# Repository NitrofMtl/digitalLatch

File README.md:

# digitalLatch

use digital latch 74ls259 to control 16 relay

With 2 74ls259 digital latch, and some logic gate, 7 GPIO pins, control 16 relay ou other type of digital outputs.
Add one more pin and 2 others 74ls259 and double to 32 outpus. Shematic included.

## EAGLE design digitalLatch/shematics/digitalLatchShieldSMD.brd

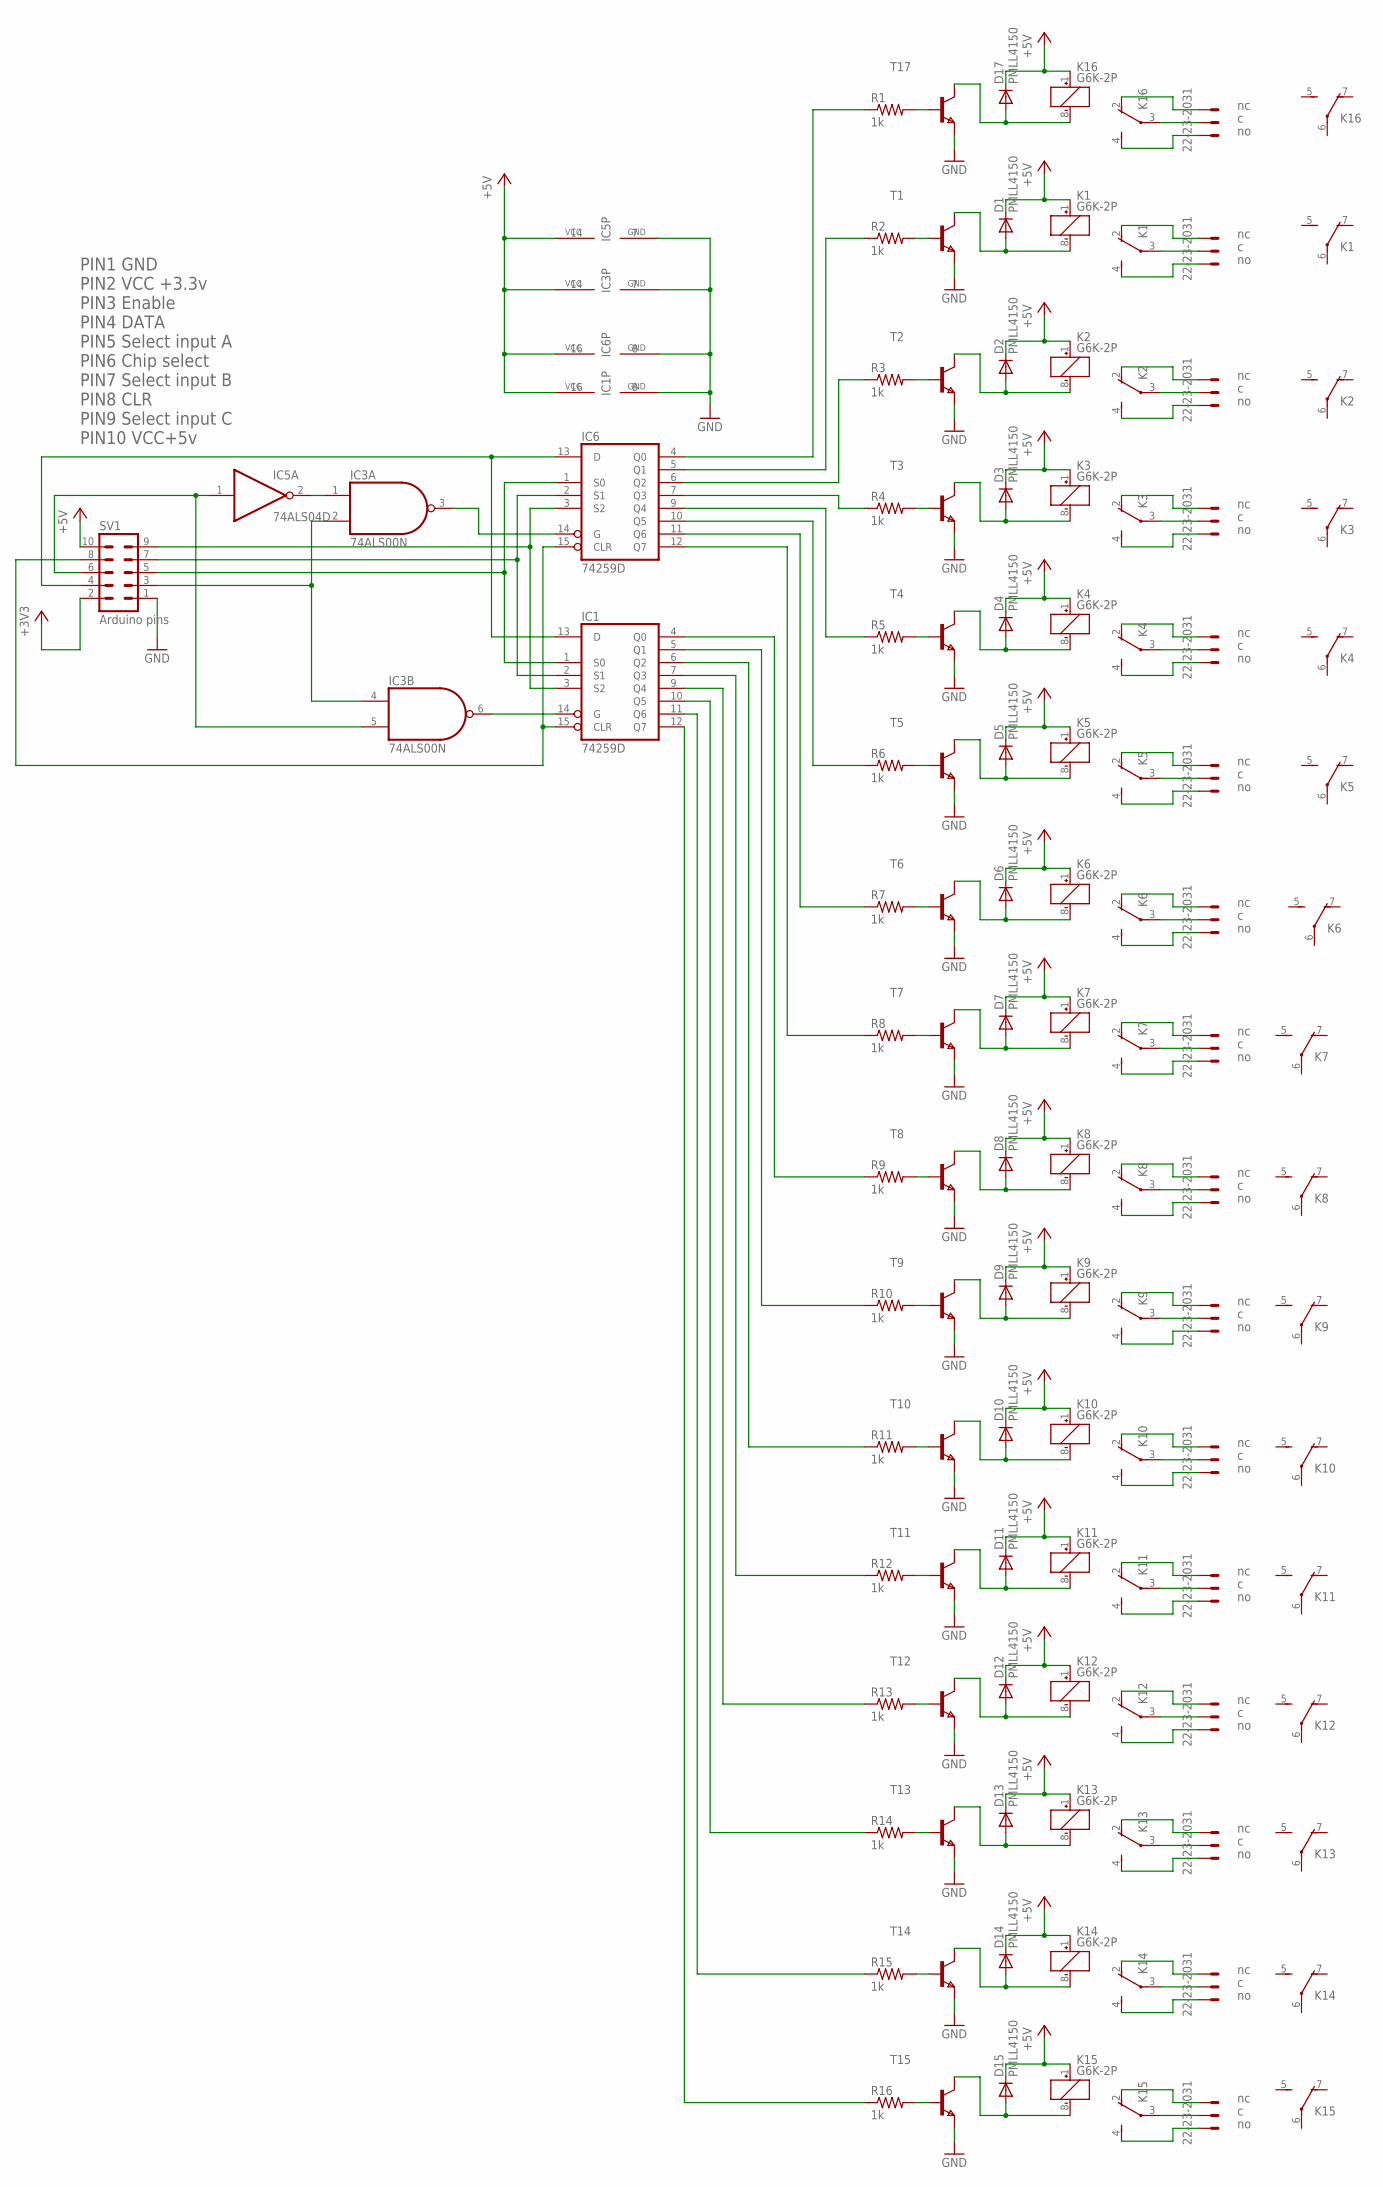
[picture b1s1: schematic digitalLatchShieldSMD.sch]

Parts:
D1, D2, D3, D4, D5, D6, D7, D8, D9, D10, D11, D12, D13, D14, D15, D17: PMLL4150; SOD80C
IC1, IC6: 74259D; SO16
IC3: 74ALS00N; DIL14
IC5: 74ALS04D; SO14
K1, K2, K3, K4, K5, K6, K7, K8, K9, K10, K11, K12, K13, K14, K15, K16: G6K-2P
R1, R2, R3, R4, R5, R6, R7, R8, R9, R10, R11, R12, R13, R14, R15, R16: 1k; M0805
SV1: Arduino pins; MA05-2
T1, T2, T3, T4, T5, T6, T7, T8, T9, T10, T11, T12, T13, T14, T15, T17: NPNSOT23; SOT-23
X1, X2, X3, X4, X5, X6, X7, X8, X9, X10, X11, X12, X13, X14, X15, X16: 22-23-2031

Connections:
+3V3: SV1.2
+5V: D1.C, D2.C, D3.C, D4.C, D5.C, D6.C, D7.C, D8.C, D9.C, D10.C, D11.C, D12.C, D13.C, D14.C, D15.C, D17.C, IC1.16 (VCC), IC3.14 (VCC), IC5.14 (VCC), IC6.16 (VCC), K1.1 (+), K2.1 (+), K3.1 (+), K4.1 (+), K5.1 (+), K6.1 (+), K7.1 (+), K8.1 (+), K9.1 (+), K10.1 (+), K11.1 (+), K12.1 (+), K13.1 (+), K14.1 (+), K15.1 (+), K16.1 (+), SV1.10
GND: IC1.8 (GND), IC3.7 (GND), IC5.7 (GND), IC6.8 (GND), SV1.1, T1.2 (E), T2.2 (E), T3.2 (E), T4.2 (E), T5.2 (E), T6.2 (E), T7.2 (E), T8.2 (E), T9.2 (E), T10.2 (E), T11.2 (E), T12.2 (E), T13.2 (E), T14.2 (E), T15.2 (E), T17.2 (E)
unnamed: IC3.3 (O), IC6.14 (G)
unnamed: IC1.14 (G), IC3.6 (O)
unnamed: IC1.3 (S2), IC6.3 (S2), SV1.9
unnamed: IC1.2 (S1), IC6.2 (S1), SV1.7
unnamed: IC1.1 (S0), IC6.1 (S0), SV1.5
unnamed: R1.2, T17.3 (B)
unnamed: K16.3, X1.2
unnamed: D17.A, K16.8 (-), T17.1 (C)
unnamed: K16.2 (O), X1.1
unnamed: K16.4 (S), X1.3
unnamed: R2.2, T1.3 (B)
unnamed: D1.A, K1.8 (-), T1.1 (C)
unnamed: K1.3, X2.2
unnamed: K1.2 (O), X2.1
unnamed: K1.4 (S), X2.3
unnamed: R3.2, T2.3 (B)
unnamed: D2.A, K2.8 (-), T2.1 (C)
unnamed: K2.3, X3.2
unnamed: K2.2 (O), X3.1
unnamed: K2.4 (S), X3.3
unnamed: R4.2, T3.3 (B)
unnamed: D3.A, K3.8 (-), T3.1 (C)
unnamed: K3.3, X4.2
unnamed: K3.2 (O), X4.1
unnamed: K3.4 (S), X4.3
unnamed: R5.2, T4.3 (B)
unnamed: D4.A, K4.8 (-), T4.1 (C)
unnamed: K4.3, X5.2
unnamed: K4.2 (O), X5.1
unnamed: K4.4 (S), X5.3
unnamed: R6.2, T5.3 (B)
unnamed: D5.A, K5.8 (-), T5.1 (C)
unnamed: K5.3, X6.2
unnamed: K5.2 (O), X6.1
unnamed: K5.4 (S), X6.3
unnamed: R7.2, T6.3 (B)
unnamed: D6.A, K6.8 (-), T6.1 (C)
unnamed: K6.3, X7.2
unnamed: K6.2 (O), X7.1
unnamed: K6.4 (S), X7.3
unnamed: R8.2, T7.3 (B)
unnamed: D7.A, K7.8 (-), T7.1 (C)
unnamed: K7.3, X8.2
unnamed: K7.2 (O), X8.1
unnamed: K7.4 (S), X8.3
unnamed: R9.2, T8.3 (B)
unnamed: D8.A, K8.8 (-), T8.1 (C)
unnamed: K8.3, X9.2
unnamed: K8.2 (O), X9.1
unnamed: K8.4 (S), X9.3
unnamed: R10.2, T9.3 (B)
unnamed: D9.A, K9.8 (-), T9.1 (C)
unnamed: K9.3, X10.2
unnamed: K9.2 (O), X10.1
unnamed: K9.4 (S), X10.3
unnamed: R11.2, T10.3 (B)
unnamed: D10.A, K10.8 (-), T10.1 (C)
unnamed: K10.3, X11.2
unnamed: K10.2 (O), X11.1
unnamed: K10.4 (S), X11.3
unnamed: R12.2, T11.3 (B)
unnamed: D11.A, K11.8 (-), T11.1 (C)
unnamed: K11.3, X12.2
unnamed: K11.2 (O), X12.1
unnamed: K11.4 (S), X12.3
unnamed: R13.2, T12.3 (B)
unnamed: D12.A, K12.8 (-), T12.1 (C)
unnamed: K12.3, X13.2
unnamed: K12.2 (O), X13.1
unnamed: K12.4 (S), X13.3
unnamed: R14.2, T13.3 (B)
unnamed: D13.A, K13.8 (-), T13.1 (C)
unnamed: K13.3, X14.2
unnamed: K13.2 (O), X14.1
unnamed: K13.4 (S), X14.3
unnamed: R15.2, T14.3 (B)
unnamed: D14.A, K14.8 (-), T14.1 (C)
unnamed: K14.3, X15.2
unnamed: K14.2 (O), X15.1
unnamed: K14.4 (S), X15.3
unnamed: R16.2, T15.3 (B)
unnamed: D15.A, K15.8 (-), T15.1 (C)
unnamed: K15.3, X16.2
unnamed: K15.2 (O), X16.1
unnamed: K15.4 (S), X16.3
unnamed: IC6.4 (Q0), R1.1
unnamed: IC6.5 (Q1), R2.1
unnamed: IC6.6 (Q2), R3.1
unnamed: IC6.7 (Q3), R4.1
unnamed: IC6.9 (Q4), R5.1
unnamed: IC6.10 (Q5), R6.1
unnamed: IC6.11 (Q6), R7.1
unnamed: IC6.12 (Q7), R8.1
unnamed: IC1.4 (Q0), R9.1
unnamed: IC1.5 (Q1), R10.1
unnamed: IC1.6 (Q2), R11.1
unnamed: IC1.7 (Q3), R12.1
unnamed: IC1.9 (Q4), R13.1
unnamed: IC1.10 (Q5), R14.1
unnamed: IC1.11 (Q6), R15.1
unnamed: IC1.12 (Q7), R16.1
unnamed: IC1.15 (CLR), IC6.15 (CLR), SV1.8
unnamed: IC3.2 (I1), IC3.4 (I0), SV1.3
unnamed: IC3.5 (I1), IC5.1 (I), SV1.6
unnamed: IC3.1 (I0), IC5.2 (O)
unnamed: IC1.13 (D), IC6.13 (D), SV1.4

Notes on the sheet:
PIN1 GND PIN2 VCC +3.3v PIN3 Enable PIN4 DATA PIN5 Select input A PIN6 Chip select PIN7 Select input B PIN8 CLR PIN9 Select input C PIN10 VCC+5v

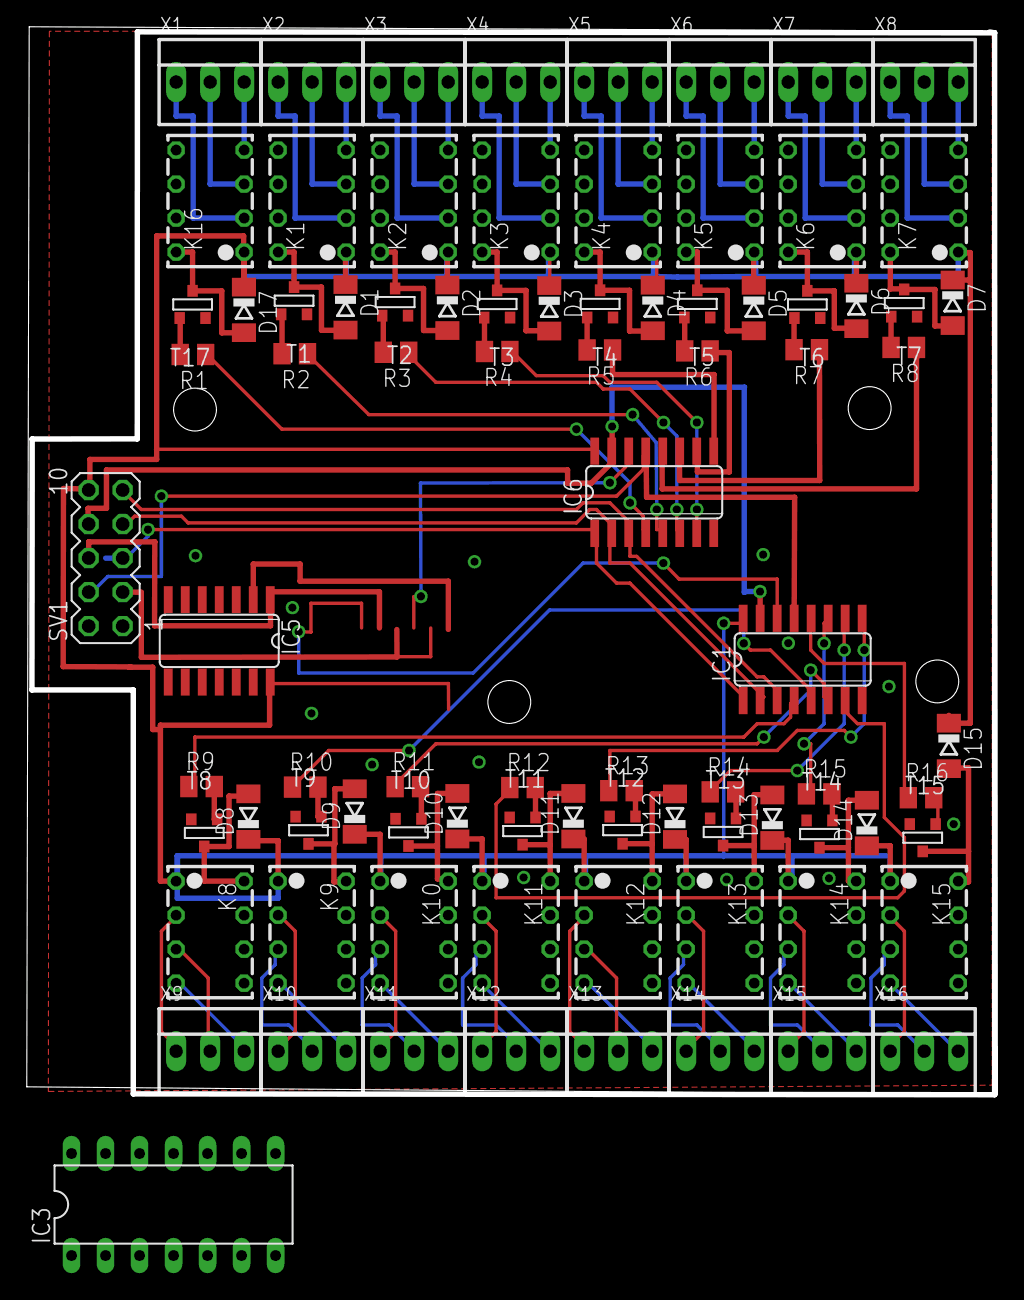
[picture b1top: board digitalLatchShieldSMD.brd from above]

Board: 2 copper layers, 72.5 x 79.8 mm, 85 parts (0 on the bottom side), 108 nets.

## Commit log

2016-04-23 Added files via upload
2017-02-27 connect to gitbash
2017-02-28 clean up
2017-04-05 cleanup folder
